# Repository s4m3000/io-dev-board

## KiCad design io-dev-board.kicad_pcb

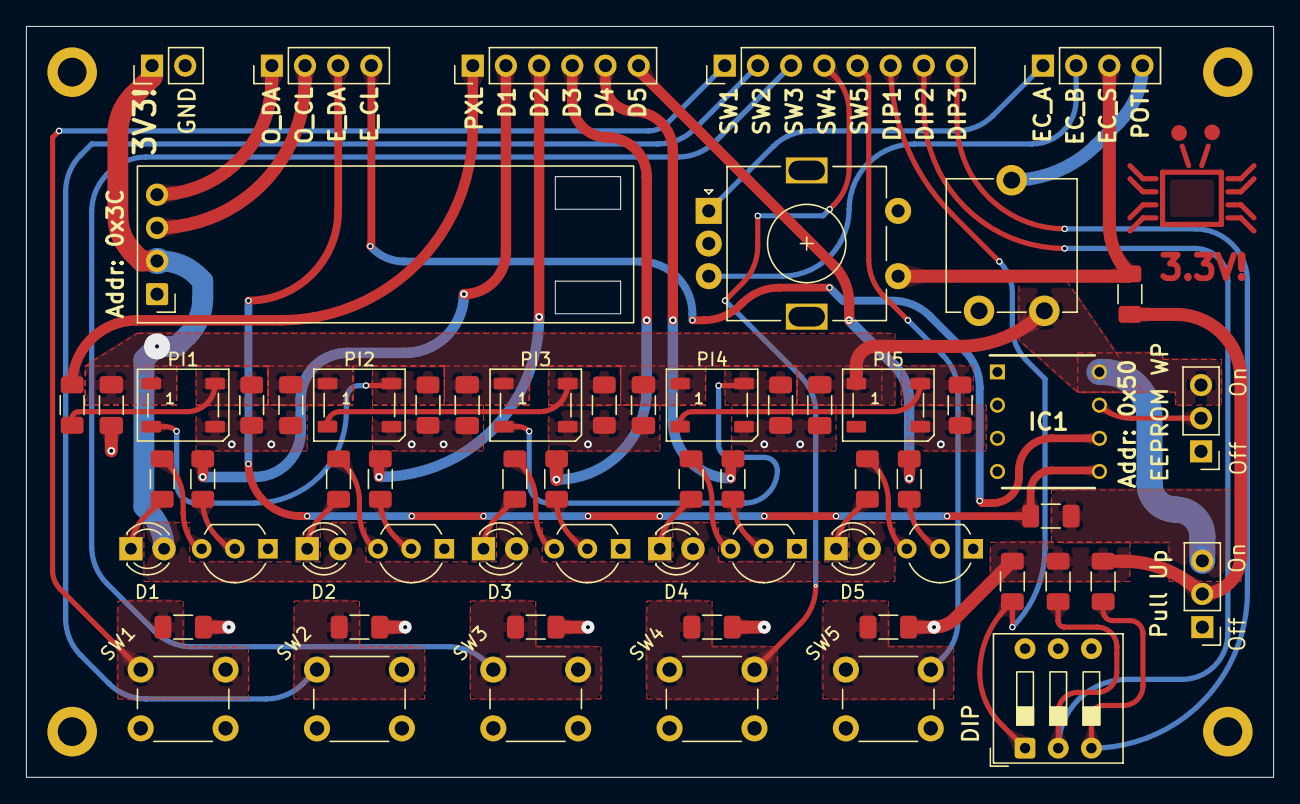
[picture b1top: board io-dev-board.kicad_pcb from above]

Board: 2 copper layers, 95.5 x 57.5 mm, 67 parts (0 on the bottom side), 46 nets.

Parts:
C1, C2, C3, C4, C5: 1uF; C_1206_3216Metric_Pad1.33x1.80mm_HandSolder
D1, D2, D3, D4, D5: LED; LED_D3.0mm
H1, H2, H3, H4: MountingHole; MountingHole_2.2mm_M2_DIN965_Pad
IC1: 24LC01B_P; DIP781W56P254L950H533Q8N
J1: PWR; PinHeader_1x02_P2.54mm_Vertical
J2: SW_Conn; PinHeader_1x08_P2.54mm_Vertical
J3: LED_Conn; PinHeader_1x06_P2.54mm_Vertical
J4: I2C_Conn; PinHeader_1x04_P2.54mm_Vertical
J5: Rot_Conn; PinHeader_1x04_P2.54mm_Vertical
JP1: Pull_Up_Jmpr; PinHeader_1x03_P2.54mm_Vertical
JP2: WP_Jmpr; PinHeader_1x03_P2.54mm_Vertical
PI1, PI2, PI3, PI4, PI5: WS2812B; LED_WS2812B_PLCC4_5.0x5.0mm_P3.2mm
Q1, Q2, Q3, Q4, Q5: Q_NPN; TO-92_Inline_Wide
R1, R2, R3, R4, R5: 55; R_1206_3216Metric_Pad1.30x1.75mm_HandSolder
R6: 2k; R_1206_3216Metric_Pad1.30x1.75mm_HandSolder
R7, R20, R21, R22, R23: 28k125; R_1206_3216Metric_Pad1.30x1.75mm_HandSolder
R8, R9, R10, R11, R12, R13, R14, R15, R16, R17, R18, R19, R24, R25: 10K; R_1206_3216Metric_Pad1.30x1.75mm_HandSolder
R26: 300; R_1206_3216Metric_Pad1.30x1.75mm_HandSolder
RV1: R_Potentiometer; Potentiometer_ACP_CA9-V10_Vertical
SW1, SW2, SW3, SW4, SW5: SW_Push; SW_PUSH_6mm_H5mm
SW6: SW_DIP_x03; SW_DIP_SPSTx03_Slide_9.78x9.8mm_W7.62mm_P2.54mm
SW7: RotaryEncoder_Switch_MP; RotaryEncoder_Alps_EC11E-Switch_Vertical_H20mm
U1: ER_OLEDM0.91_1x-I2C

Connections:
+3V3: C1.1, C2.1, C3.1, C4.1, C5.1, D1.2 (A), D2.2 (A), D3.2 (A), D4.2 (A), D5.2 (A), IC1.8 (VCC), J1.1, JP1.3 (B), JP2.3 (B), PI1.1 (VDD), PI2.1 (VDD), PI3.1 (VDD), PI4.1 (VDD), PI5.1 (VDD), R6.1, RV1.1, U1.2 (VCC)
/DIP_1: J2.6, R11.2, SW6.1
/DIP_2: J2.7, R12.2, SW6.2
/DIP_3: J2.8, R13.2, SW6.3
/EC_A: J5.1, SW7.A
/EC_B: J5.2, SW7.B
/EC_S: J5.3, R14.2, SW7.S1
/EEPROM_SCL: IC1.6 (SCL), J4.4
/EEPROM_SDA: IC1.5 (SDA), J4.3, R6.2
/LED_1: J3.2, R7.1
/LED_2: J3.3, R20.1
/LED_3: J3.4, R21.1
/LED_4: J3.5, R22.1
/LED_5: J3.6, R23.1
/OLED_SCL: J4.2, U1.3 (SCL)
/OLED_SDA: J4.1, U1.4 (SDA)
/PIXEL_IN: J3.1, R26.1
/POTI: J5.4, RV1.2
/PULL_UP: JP1.2 (C), R11.1, R12.1, R13.1, R14.1, R15.1, R16.1, R17.1, R18.1, R19.1
/SW_1: J2.1, R15.2, SW1.1
/SW_2: J2.2, R16.2, SW2.1
/SW_3: J2.3, R17.2, SW3.1
/SW_4: J2.4, R18.2, SW4.1
/SW_5: J2.5, R19.2, SW5.1
/WP: IC1.7 (WP), JP2.2 (C)
GND: C1.2, C2.2, C3.2, C4.2, C5.2, IC1.4 (VSS), J1.2, JP2.1 (A), PI1.3 (VSS), PI2.3 (VSS), PI3.3 (VSS), PI4.3 (VSS), PI5.3 (VSS), Q1.1 (E), Q2.1 (E), Q3.1 (E), Q4.1 (E), Q5.1 (E), R8.2, R9.2, R10.2, R24.2, R25.2, RV1.3, SW1.2, SW2.2, SW3.2, SW4.2, SW5.2, SW6.4, SW6.5, SW6.6, SW7.C, SW7.MP, SW7.S2, U1.1 (GND)
unnamed: D1.1 (K), R1.1
unnamed: D2.1 (K), R2.1
unnamed: D3.1 (K), R3.1
unnamed: D4.1 (K), R4.1
unnamed: D5.1 (K), R5.1
unnamed: PI1.4 (DIN), R8.1, R26.2
unnamed: PI1.2 (DOUT), PI2.4 (DIN), R9.1
unnamed: PI2.2 (DOUT), PI3.4 (DIN), R10.1
unnamed: PI3.2 (DOUT), PI4.4 (DIN), R24.1
unnamed: PI4.2 (DOUT), PI5.4 (DIN), R25.1
unnamed: Q1.2 (B), R7.2
unnamed: Q1.3 (C), R1.2
unnamed: Q2.2 (B), R20.2
unnamed: Q2.3 (C), R2.2
unnamed: Q3.2 (B), R21.2
unnamed: Q3.3 (C), R3.2
unnamed: Q4.2 (B), R22.2
unnamed: Q4.3 (C), R4.2
unnamed: Q5.2 (B), R23.2
unnamed: Q5.3 (C), R5.2

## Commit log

2026-04-01 add '3.3V!' label to board, remove floating 'not connected' mark
2026-04-02 fix: pin order for NPN transistors
2026-04-02 feat: refill copper areas
2026-04-02 refactor: rearrange labels
2026-04-02 refactor: align transistors with LEDs
2026-04-02 refactor: reposition some vias
2026-04-17 refactor: add LED and NPN resistor calculation hints
2026-04-17 fix: add missing 'I_C' to resistor calculation
